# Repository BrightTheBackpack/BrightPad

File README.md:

# BrightPad

## Audio Control Macropad

### Features

9 Switches

128x32 OLED Display

Mute Volume, Lower/Raise volume, Play/Pause, Skip, Go Back, Toggle Lights, Blank, writes "test"

Displays the Time

### CAD
Designed in Fusion

Two parts, fitted together with 4 M3 Screws

### PCB

Designed in KiCad

Schematic:

PCB:

### BOM
9x MX Switches
1x Seeed XIAO RP2040
9x Through-hole 1N4148 Diodes
1x 0.91 inch OLED Display
9x DSA Keycaps
9x SK6812 MINI-E LEDs
4x M3x16mm screws
4x Heatset Inserts
1x 3d Printed Case

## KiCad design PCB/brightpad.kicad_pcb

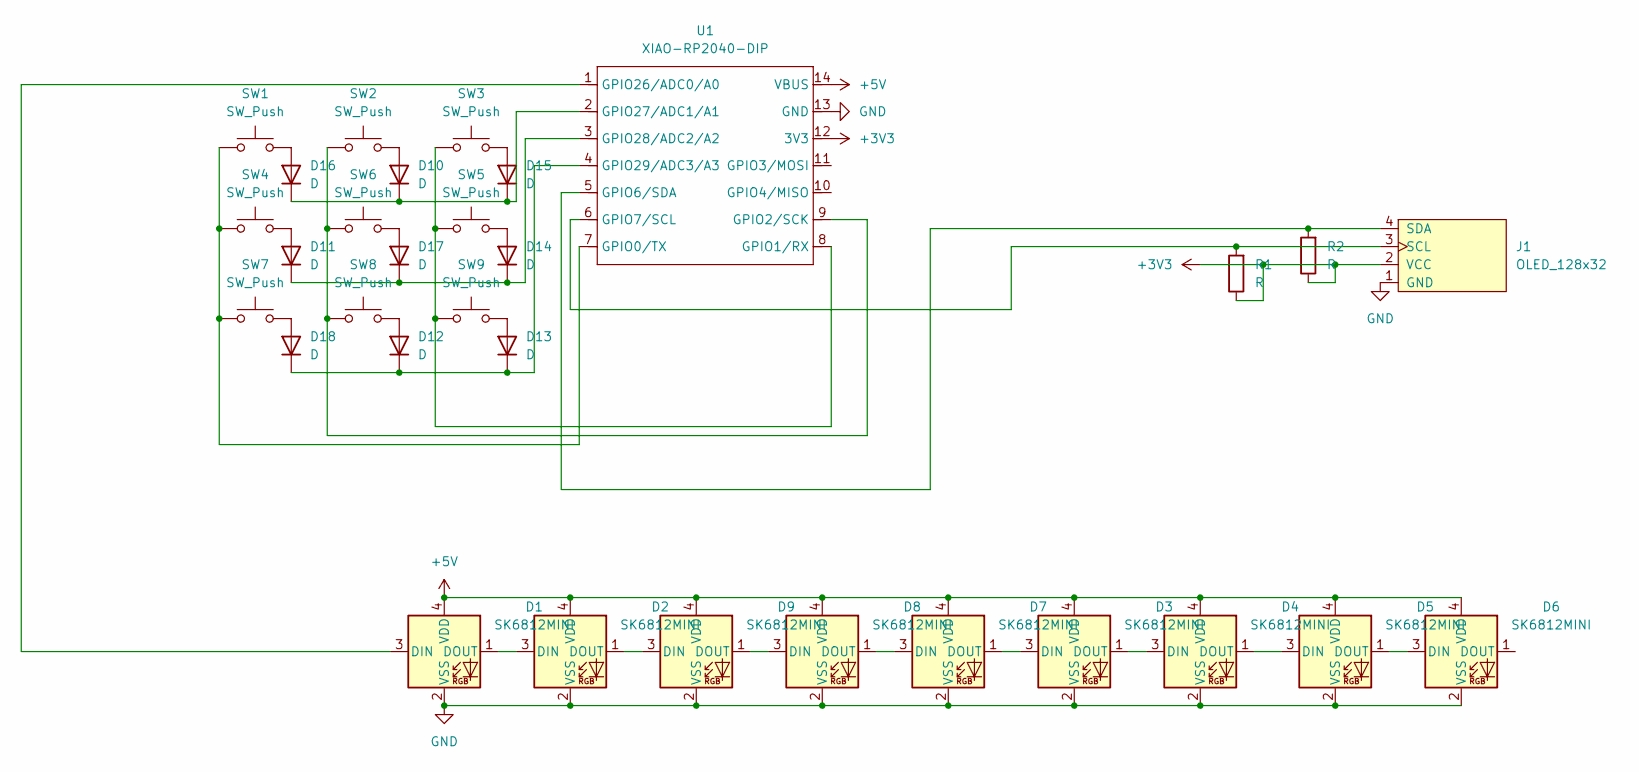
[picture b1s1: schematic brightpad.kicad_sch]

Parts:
D1, D2, D3, D4, D5, D6, D7, D8, D9: SK6812MINI; SK6812MINI-E
D10, D11, D12, D13, D14, D15, D16, D17, D18: D; D_DO-35_SOD27_P7.62mm_Horizontal
J1: OLED_128x32
R1, R2: R; R_Axial_DIN0204_L3.6mm_D1.6mm_P7.62mm_Horizontal
SW1, SW2, SW3, SW4, SW5, SW6, SW7, SW8, SW9: SW_Push; MX_PCB_1.00u
U1: XIAO-RP2040-DIP

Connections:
+3V3: J1.2 (VCC), R1.1, R2.1, U1.12 (3V3)
+5V: D1.4 (VDD), D2.4 (VDD), D3.4 (VDD), D4.4 (VDD), D5.4 (VDD), D6.4 (VDD), D7.4 (VDD), D8.4 (VDD), D9.4 (VDD), U1.14 (VBUS)
GND: D1.2 (VSS), D2.2 (VSS), D3.2 (VSS), D4.2 (VSS), D5.2 (VSS), D6.2 (VSS), D7.2 (VSS), D8.2 (VSS), D9.2 (VSS), J1.1 (GND), U1.13 (GND)
unnamed: D1.3 (DIN), U1.1 (GPIO26/ADC0/A0)
unnamed: D1.1 (DOUT), D2.3 (DIN)
unnamed: D2.1 (DOUT), D9.3 (DIN)
unnamed: D3.3 (DIN), D7.1 (DOUT)
unnamed: D3.1 (DOUT), D4.3 (DIN)
unnamed: D4.1 (DOUT), D5.3 (DIN)
unnamed: D5.1 (DOUT), D6.3 (DIN)
unnamed: D7.3 (DIN), D8.1 (DOUT)
unnamed: D8.3 (DIN), D9.1 (DOUT)
unnamed: D10.2 (A), SW2.2
unnamed: D10.1 (K), D15.1 (K), D16.1 (K), U1.2 (GPIO27/ADC1/A1)
unnamed: D11.2 (A), SW4.2
unnamed: D11.1 (K), D14.1 (K), D17.1 (K), U1.3 (GPIO28/ADC2/A2)
unnamed: D12.2 (A), SW8.2
unnamed: D12.1 (K), D13.1 (K), D18.1 (K), U1.4 (GPIO29/ADC3/A3)
unnamed: D13.2 (A), SW9.2
unnamed: D14.2 (A), SW5.2
unnamed: D15.2 (A), SW3.2
unnamed: D16.2 (A), SW1.2
unnamed: D17.2 (A), SW6.2
unnamed: D18.2 (A), SW7.2
unnamed: J1.3 (SCL), R1.2, U1.6 (GPIO7/SCL)
unnamed: J1.4 (SDA), R2.2, U1.5 (GPIO6/SDA)
unnamed: SW1.1, SW4.1, SW7.1, U1.7 (GPIO0/TX)
unnamed: SW3.1, SW5.1, SW9.1, U1.8 (GPIO1/RX)
unnamed: SW2.1, SW6.1, SW8.1, U1.9 (GPIO2/SCK)

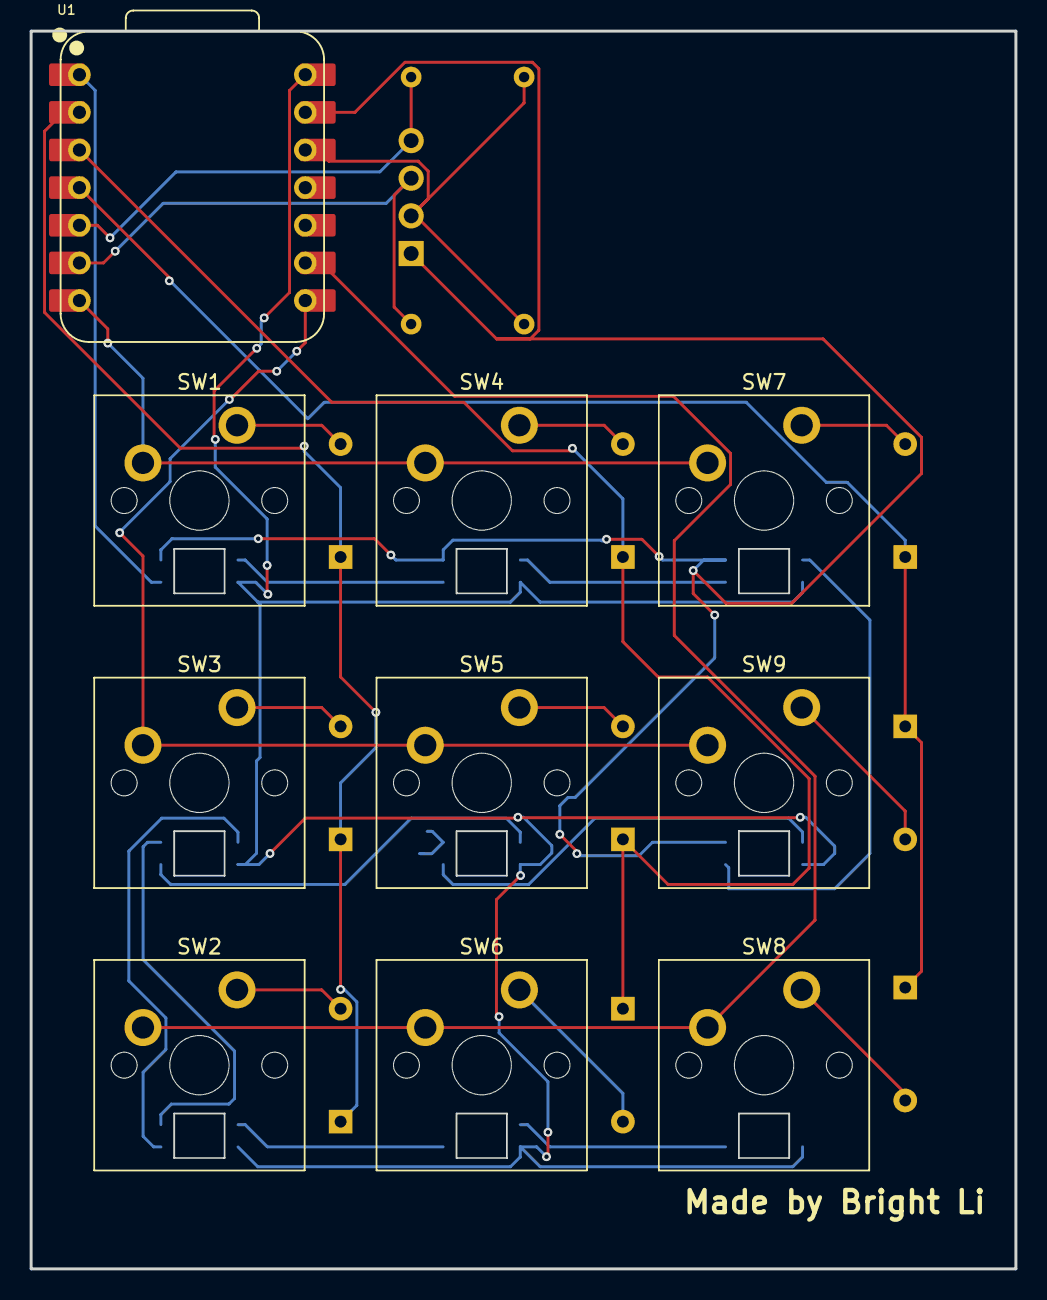
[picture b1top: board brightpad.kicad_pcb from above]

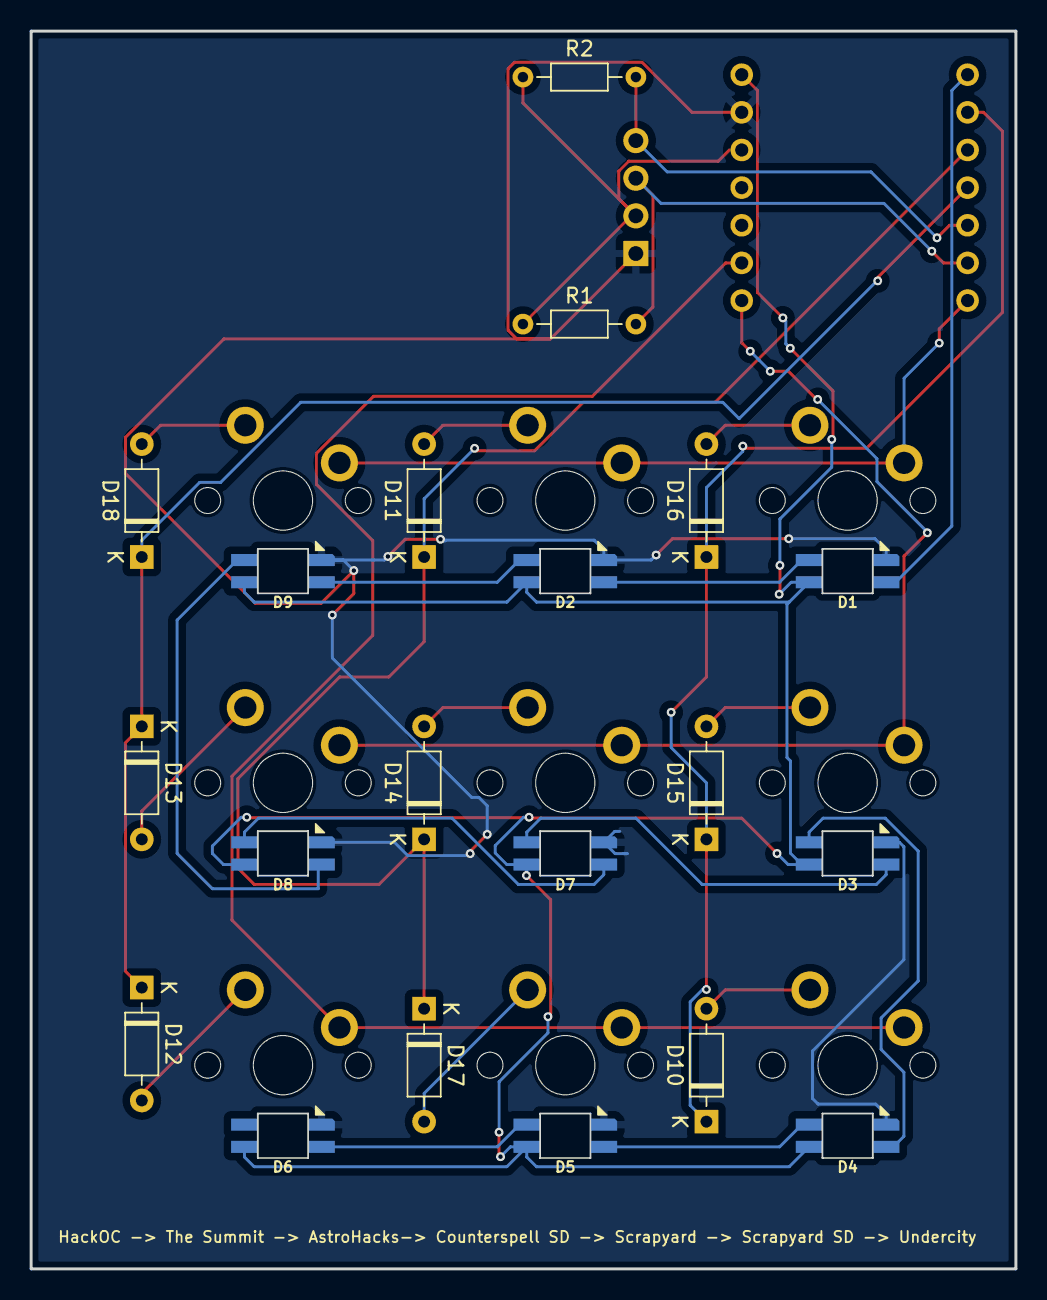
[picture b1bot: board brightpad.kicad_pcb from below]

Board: 2 copper layers, 66.4 x 83.5 mm, 31 parts (20 on the bottom side), 29 nets.

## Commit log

2025-06-29 add all files
